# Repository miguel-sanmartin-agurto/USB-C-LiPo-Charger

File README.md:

# USB-C LiPo Charger

A minimal, single-cell (1S) LiPo battery charger powered by a USB-C input. This project is designed to be a simple, low-cost, and compact charging solution for hobbyist electronics.

[Download the full Schematic (PDF)](USB-C-LiPo-Charger_sch.pdf)

## 🚀 Project Overview
This circuit provides a safe and reliable way to charge 1S LiPo batteries using any standard 5V USB-C power source. It's built around the **MCP73831** charge controller, which handles the complete charging algorithm (pre-conditioning, constant current, constant voltage) to protect the battery.

## ✨ Features

* **Input:** USB-C (5V)
* **Charge Controller:** MCP73831 (or LTH7R)
* **Charge Current:** 500mA (set by a single resistor, R3)
* **Output:** 2-pin JST-PH Connector for 1S LiPo batteries
* **Indicator:** On-board 'Charging' status LED (On when charging, Off when complete)
* **Protection:** Utilizes the MCP73831's internal safety features and Si2319CDS for reverse polarity protection.

## ⚡ Schematic

The circuit is intentionally simple, requiring only the charge controller, a USB-C port, and a few passive components.

## 🛠️ Fabrication

The Gerbers files (`.gbr` and `.drl`) needed to manufacture this PCB are located in the `/gerbers` directory of this repository. You can upload the `.zip` file from that folder directly to any PCB manufacturer (like JLCPCB, PCBWay, etc.).

* **PCB Dimensions:** [12mm x 28.5mm]
* **Layers:** 2 (Top and Bottom)
* **Default Copper:** 1 oz/ft²

## 📜 License

This project is open-source. Feel free to use, modify, and distribute it.

---
*Project by Miguel San Martin*

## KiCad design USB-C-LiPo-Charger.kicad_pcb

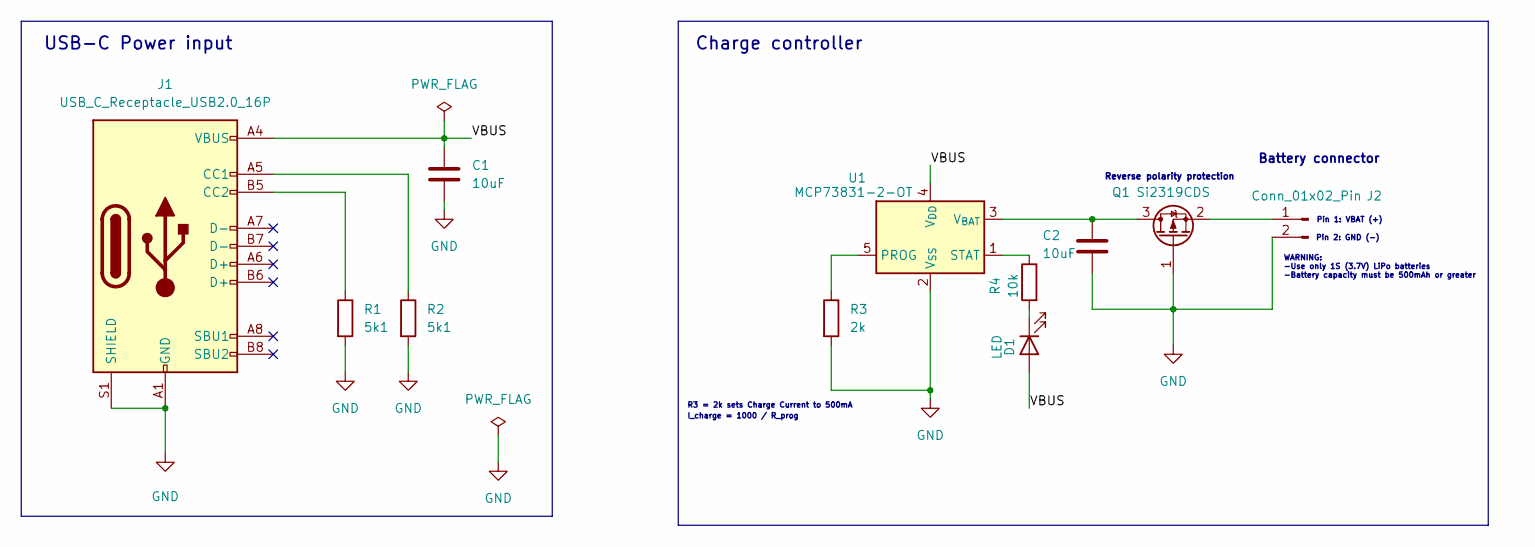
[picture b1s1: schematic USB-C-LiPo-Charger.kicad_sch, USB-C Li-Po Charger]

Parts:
C1, C2: 10uF; C_0805_2012Metric
D1: LED; LED_0603_1608Metric
J1: USB_C_Receptacle_USB2.0_16P; USB_C_Receptacle_HRO_TYPE-C-31-M-12
J2: Conn_01x02_Pin; JST_PH_B2B-PH-K_1x02_P2.00mm_Vertical
Q1: Si2319CDS; SOT-23
R1, R2: 5k1; R_0603_1608Metric_Pad0.98x0.95mm_HandSolder
R3: 2k; R_0603_1608Metric_Pad0.98x0.95mm_HandSolder
R4: 10k; R_0603_1608Metric_Pad0.98x0.95mm_HandSolder
U1: MCP73831-2-OT; SOT-23-5

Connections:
/VBUS: C1.1, D1.2 (A), J1.A4 (VBUS), J1.A9 (VBUS), J1.B4 (VBUS), J1.B9 (VBUS), U1.4 (V_{DD})
GND: C1.2, C2.2, J1.A1 (GND), J1.A12 (GND), J1.B1 (GND), J1.B12 (GND), J1.S1 (SHIELD), J2.2, Q1.1 (G), R1.2, R2.2, R3.2, U1.2 (V_{SS})
unnamed: D1.1 (K), R4.2
unnamed: J1.A5 (CC1), R2.1
unnamed: J1.B5 (CC2), R1.1
unnamed: J2.1, Q1.2 (S)
unnamed: C2.1, Q1.3 (D), U1.3 (V_{BAT})
unnamed: R3.1, U1.5 (PROG)
unnamed: R4.1, U1.1 (STAT)

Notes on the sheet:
Pin 2: GND (-)
Reverse polarity protection
WARNING: -Use only 1S (3.7V) LiPo batteries -Battery capacity must be 500mAh or greater
I_charge = 1000 / R_prog
USB-C Power input
Charge controller
R3 = 2k sets Charge Current to 500mA
Pin 1: VBAT (+)
Battery connector

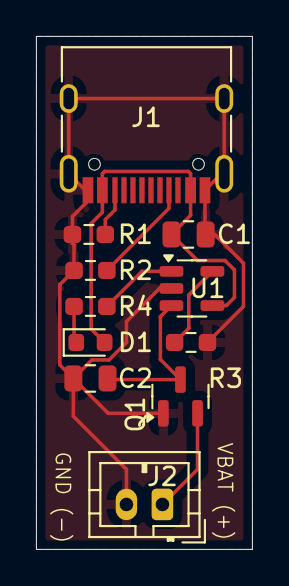
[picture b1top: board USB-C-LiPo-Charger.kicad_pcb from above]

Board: 2 copper layers, 12.0 x 28.5 mm, 11 parts (0 on the bottom side), 9 nets.

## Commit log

2025-11-14 Initial project commit v1.1
2025-11-14 File has been fixed
